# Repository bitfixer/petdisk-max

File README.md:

# petdisk-max
Firmware and schematics for the PETdisk MAX storage device for Commodore PET

The PETdisk MAX is a storage device for the Commodore PET series of computers. It can use both a microSD card and can also access up to 4 network drives.
The network drives are essentially directories of files hosted on standard web servers. They can be configured as read/write or readonly. Currently PHP support is required on a web server to be used as a network drive - simply copy the [petdisk.php](https://raw.githubusercontent.com/bitfixer/petdisk-max/main/www/petdisk.php) file into a directory on a web server along with some PET files, and you're ready to go.

## Installation

The PETdisk MAX plugs into the IEEE-488 port on the back of your PET. Looking at the back of the PET, this is the edge connector on the right side.
Since the IEEE-488 port does not supply power, a separate power connection is required.
Depending on when you received your PETdisk MAX, this will either be a small board which fits into one of the PET's ROM sockets and provides a 5v power pin, or a clip which connects to the PETdisk with a wire lead.

First, open up the PET.

### For the ROM socket: 
If you have any ROM sockets free, choose the one closest to the PETdisk and install the board into the socket on the mainboard, making sure to align the notches on both sockets. 
If no ROM sockets are free, first remove a ROM chip from the mainboard, install the socket, and then reinstall the ROM chip into the new socket. Make sure to line the notches up.
Then connect the wire lead included with the PETdisk to the 5v pin, and feed the other end out the back of the PET through the opening around the IEEE-488 connector.

### For the clip: 
You'll need to clip onto a 5v source on the mainboard. An easy place to find this is on one of the 6520 chips, there are 2 of them in the PET. They are located close on the board to the IEEE-488 port. Locate one of the 6520 chips, they will be close to the back of the board and labeled '6520' somewhere on the chip. Not to be confused with the '6502' also on the board.

Locations of 6520s in some PET motherboards:\
2001: UB8 and UG8\
2001N: UC6 and UC7\
8032: UB16 and UB12

Pick the more conveniently located 6520, and find pin 20. If you are looking at the chip with the notch up, go to the left side of the chip and go down to the lower left corner. Clip on to this pin and then feed the wire lead out the back through the opening around the IEEE-488 connector.
If you prefer, you can clip on to any capacitor lead connected to 5v in the computer, there are several. 

Moving to the back of the PET, connect the wire lead to the PETdisk MAX. There is a connector on the back of the PETdisk, and the position on the connector furthest to the right side of the device is labeled '5v'. Connect here, double check that you are connected in the furthest right position, closest to the edge of the board.

After this, just plug the PETdisk MAX into the IEEE-488 connector and you're ready to go.

## Configuration

The default configuration of the PETdisk MAX uses the built-in sd card as device 8.
You can change this device number as well as setting up a maximum of 4 network drives by editing this file template:
[PETDISK.CFG](https://raw.githubusercontent.com/bitfixer/petdisk-max/main/PETDISK.CFG)\
Each line of the file consists of the drive number, comma, text specifying the drive.
SD0 refers to the built-in SD card. Change the drive number here if you like.
For network drives, the specifier is the full URL of the drive script. Up to 4 can be used at once.
Remove any lines with URLs if you don't want to use any network drives at that time.

The last 2 lines of the file contain the ssid and password for your wifi network, replace the placeholders with the information for your network. Note that only 2.4 Ghz wifi networks are supported.

Copy the edited file onto the root directory of your SD card. On the next power up, the new configuration will be read.

## Operation

Basic drive operations are the same as other Commodore storage devices.
Load a directory with
LOAD"$",devicenumber
and 
LIST

For BASIC 4, the CATALOG and DIRECTORY commands will also work.

Load a program (.PRG) with
LOAD"PROGRAM",devicenumber

or save with
SAVE"PROGRAM",devicenumber

The DLOAD command also works.

## Subdirectories

To change directories on a FAT32 volume, use
LOAD"$:dirname",devicenumber

This also loads the directory listing of the new directory.

Return to the previous directory with
LOAD"$:..",devicenumber

## D64

The PETdisk MAX currently supports D64 files for both reading and writing.
To mount a D64 file stored on either an SD card or network drive,
use the following command:
LOAD"$:filename.d64",devicenumber

This will mount the D64 file as the disk for the specified device number. It will also load the directory of the disk image which can be viewed with LIST.

To unmount the D64 file and return to the original device, use
LOAD"$:..",devicenumber

## Updating the PETdisk MAX

Firmware updates will come periodically with fixes and new features. The latest firmware for both the v1 and v2 PETdisk MAX models will be located here:\
PETdisk MAX v1 (Atmel ATmega1284)
[FIRMWARE.BIN](https://github.com/bitfixer/petdisk-max/raw/main/firmware/FIRMWARE.BIN)

PETdisk MAX v2 (ESP32):
[FIRMWARE.PD2](https://github.com/bitfixer/petdisk-max/raw/main/firmware/FIRMWARE.PD2)

To update the firmware on the device, copy this file onto the root directory of an empty microSD card formatted to FAT32. Insert the card into the PETdisk and power up. On the v1, the new firmware will be loaded onto the device after a few seconds. On the v2, the update takes about a minute during which you will first see rapid blinking on the LED, then a single blink every few seconds, followed by a few additional blinks and then the LED remains on. Once the LED is solidly on, the update is done.\
You can verify that the update worked by loading a directory from the SD card. 
At the end of the directory listing the git commit id will be listed, so you can verify it changed from before the update. This also provides a firmware ID which you can use if you need to report any bugs.

## Building the PETdisk MAX firmware

If you want to build the PETdisk MAX firmware, two versions are included in this repo. The first is a legacy version built with platformio and arduino, and is located in the 'legacy' directory. Open that directory in VSCode with the platformio plugin installed, and you should be able to build and install with the platformio menu. 
Second is a newer version built directly on esp-idf v5.1+. This is located in the 'idf' directory. With esp-idf 5.1+ installed and sourced, run 'idf.py build flash' to build and install the firmware on the device.

## Coming Soon

Things known to currently not work (but working on it):
1. Support for BASIC 1 ROM (i.e. non-upgraded original PET 2001)
2. REL files
3. U2 (block write) drive command

Please let me know if you discover any bugs or have feature requests.
bitfixer at (removeforantispam) bitfixer dot com

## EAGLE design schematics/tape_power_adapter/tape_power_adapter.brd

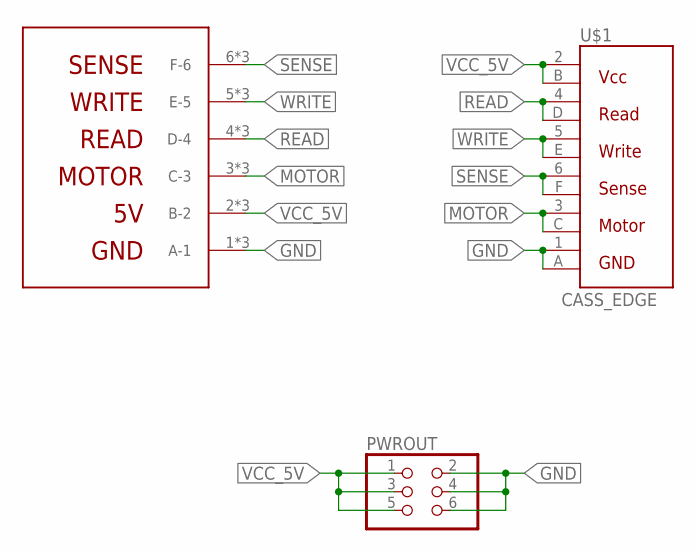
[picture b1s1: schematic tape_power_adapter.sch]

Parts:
PWROUT: PINHD-2X03_2.54; 2X03
U$1: CASS_EDGE; 12PINEDGE
U$2: C64CASSCONN; C64TAPECONN

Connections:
GND: PWROUT.2, PWROUT.4, PWROUT.6, U$1.1 (GND1), U$1.A (GND2), U$2.1 (A-1), U$2.1A (A-1), U$2.A (A-1)
MOTOR: U$1.3 (MOTOR1), U$1.C (MOTOR2), U$2.3 (C-3), U$2.3C (C-3), U$2.C (C-3)
READ: U$1.4 (READ1), U$1.D (READ2), U$2.4 (D-4), U$2.4D (D-4), U$2.D (D-4)
SENSE: U$1.6 (SENSE1), U$1.F (SENSE2), U$2.6 (F-6), U$2.6F (F-6), U$2.F (F-6)
VCC_5V: PWROUT.1, PWROUT.3, PWROUT.5, U$1.2 (VCC1), U$1.B (VCC2), U$2.2 (B-2), U$2.2B (B-2), U$2.B (B-2)
WRITE: U$1.5 (WRITE1), U$1.E (WRITE2), U$2.5 (E-5), U$2.5E (E-5), U$2.E (E-5)

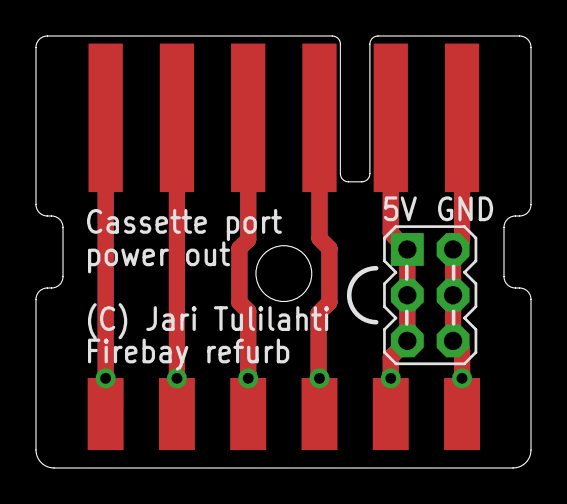
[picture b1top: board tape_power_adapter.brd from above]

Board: 2 copper layers, 27.5 x 24.0 mm, 3 parts (0 on the bottom side), 6 nets.

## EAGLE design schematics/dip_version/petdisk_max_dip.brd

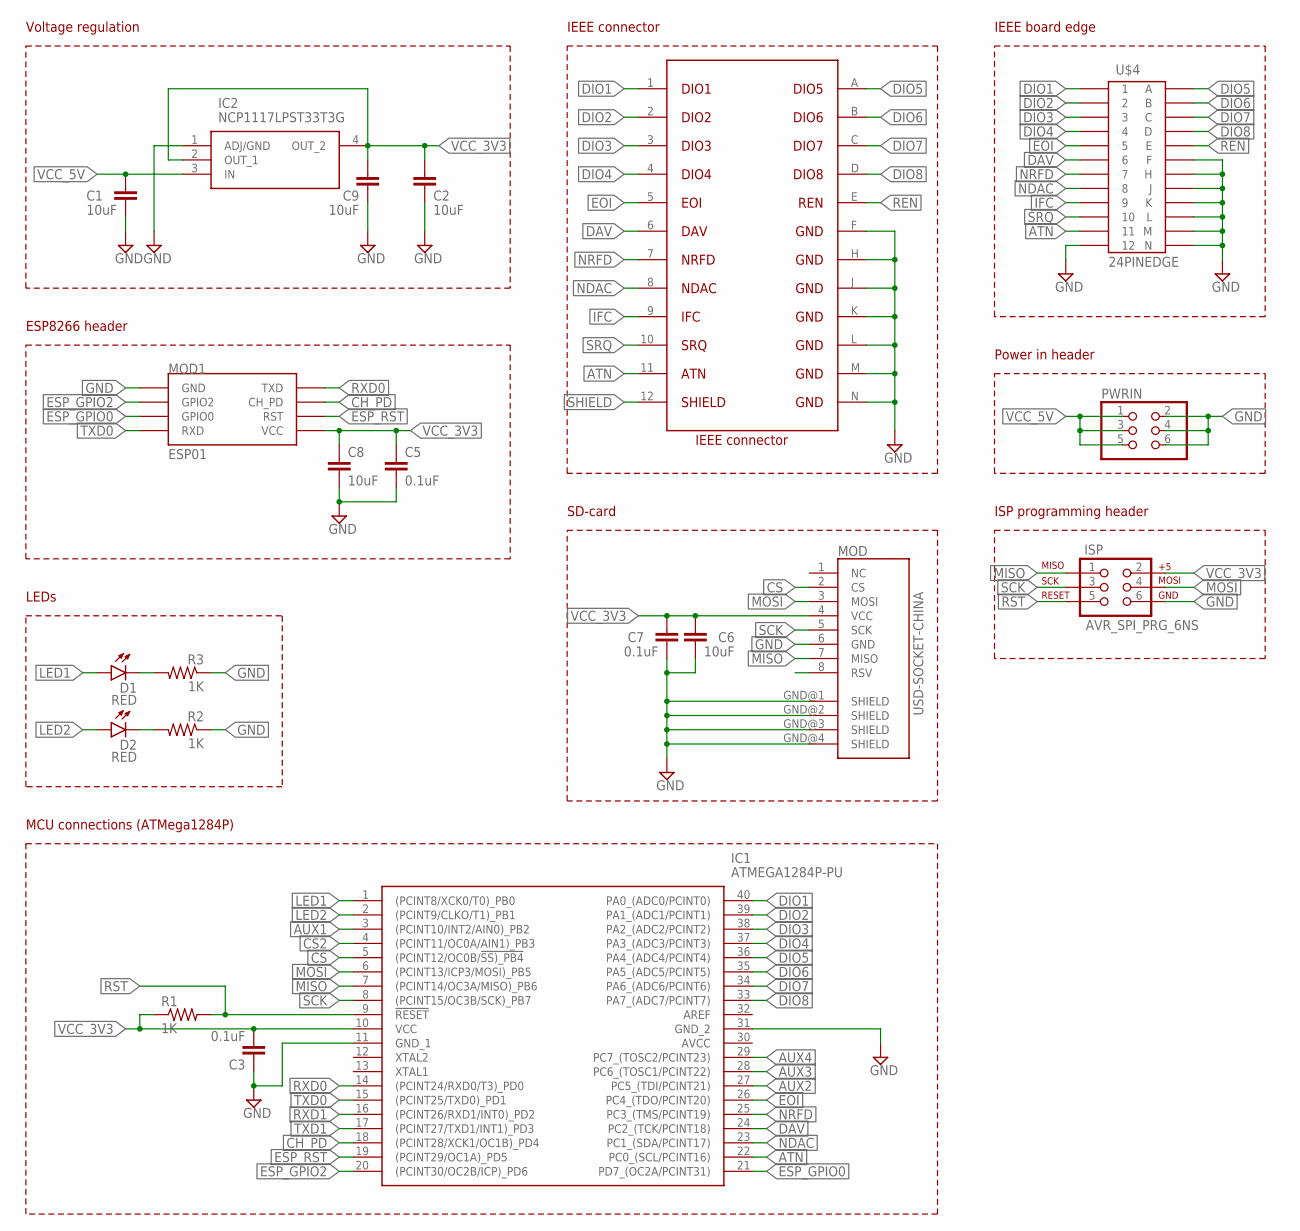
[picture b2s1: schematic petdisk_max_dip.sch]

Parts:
C1, C2, C6, C8, C9: 10uF; 1206
C3, C5, C7: 0.1uF; 0603-CAP
D1, D2: RED; LED-0603
IC1: ATMEGA1284P-PU; DIP1543W58P254L5175H635Q40N
IC2: NCP1117LPST33T3G; SOT230P700X180-4N
ISP: AVR_SPI_PRG_6NS; 2X3-NS
MOD: USD-SOCKET-CHINA; USD-SOCKET-PP
MOD1: ESP01
PWRIN: PINHD-2X03_2.54; 2X03
R1, R2, R3: 1K; 0603-RES
U$1: CBM_IEEE_CONN; UPS24CONN
U$4: 24PINEDGE

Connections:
ATN: IC1.22 (PC0_(SCL/PCINT16)), U$1.11, U$4.11
AUX1: IC1.3 ((PCINT10/INT2/AIN0)_PB2)
AUX2: IC1.27 (PC5_(TDI/PCINT21))
AUX3: IC1.28 (PC6_(TOSC1/PCINT22))
AUX4: IC1.29 (PC7_(TOSC2/PCINT23))
CH_PD: IC1.18 ((PCINT28/XCK1/OC1B)_PD4), MOD1.CH_PD
CS: IC1.5 ((PCINT12/OC0B/!SS)_PB4), MOD.2 (CS)
CS2: IC1.4 ((PCINT11/OC0A/AIN1)_PB3)
DAV: IC1.24 (PC2_(TCK/PCINT18)), U$1.6, U$4.6
DIO1: IC1.40 (PA0_(ADC0/PCINT0)), U$1.1, U$4.1
DIO2: IC1.39 (PA1_(ADC1/PCINT1)), U$1.2, U$4.2
DIO3: IC1.38 (PA2_(ADC2/PCINT2)), U$1.3, U$4.3
DIO4: IC1.37 (PA3_(ADC3/PCINT3)), U$1.4, U$4.4
DIO5: IC1.36 (PA4_(ADC4/PCINT4)), U$1.A, U$4.A
DIO6: IC1.35 (PA5_(ADC5/PCINT5)), U$1.B, U$4.B
DIO7: IC1.34 (PA6_(ADC6/PCINT6)), U$1.C, U$4.C
DIO8: IC1.33 (PA7_(ADC7/PCINT7)), U$1.D, U$4.D
EOI: IC1.26 (PC4_(TDO/PCINT20)), U$1.5, U$4.5
ESP_GPIO0: IC1.21 (PD7_(OC2A/PCINT31)), MOD1.GPIO0
ESP_GPIO2: IC1.20 ((PCINT30/OC2B/ICP)_PD6), MOD1.GPIO2
ESP_RST: IC1.19 ((PCINT29/OC1A)_PD5), MOD1.RST
GND: C1.2, C2.2, C3.1, C5.2, C6.2, C7.2, C8.2, C9.2, IC1.11 (GND_1), IC1.31 (GND_2), IC2.1 (ADJ/GND), ISP.6, MOD.6 (GND), MOD.GND@1 (SHIELD), MOD.GND@2 (SHIELD), MOD.GND@3 (SHIELD), MOD.GND@4 (SHIELD), MOD1.GND, PWRIN.2, PWRIN.4, PWRIN.6, R2.1, R3.1, U$1.F, U$1.H, U$1.J, U$1.K, U$1.L, U$1.M, U$1.N, U$4.12, U$4.F, U$4.H, U$4.J, U$4.K, U$4.L, U$4.M, U$4.N
IFC: U$1.9, U$4.9
LED1: D1.A, IC1.1 ((PCINT8/XCK0/T0)_PB0)
LED2: D2.A, IC1.2 ((PCINT9/CLKO/T1)_PB1)
MISO: IC1.7 ((PCINT14/OC3A/MISO)_PB6), ISP.1, MOD.7 (MISO)
MOSI: IC1.6 ((PCINT13/ICP3/MOSI)_PB5), ISP.4, MOD.3 (MOSI)
unnamed: D1.C, R3.2
unnamed: D2.C, R2.2
NDAC: IC1.23 (PC1_(SDA/PCINT17)), U$1.8, U$4.8
NRFD: IC1.25 (PC3_(TMS/PCINT19)), U$1.7, U$4.7
REN: U$1.E, U$4.E
RST: IC1.9 (!RESET), ISP.5, R1.2
RXD0: IC1.14 ((PCINT24/RXD0/T3)_PD0), MOD1.TX (TXD)
RXD1: IC1.16 ((PCINT26/RXD1/INT0)_PD2)
SCK: IC1.8 ((PCINT15/OC3B/SCK)_PB7), ISP.3, MOD.5 (SCK)
SHIELD: U$1.12
SRQ: U$1.10, U$4.10
TXD0: IC1.15 ((PCINT25/TXD0)_PD1), MOD1.RX (RXD)
TXD1: IC1.17 ((PCINT27/TXD1/INT1)_PD3)
VCC_3V3: C2.1, C3.2, C5.1, C6.1, C7.1, C8.1, C9.1, IC1.10 (VCC), IC2.2 (OUT_1), IC2.4 (OUT_2), ISP.2, MOD.4 (VCC), MOD1.VCC, R1.1
VCC_5V: C1.1, IC2.3 (IN), PWRIN.1, PWRIN.3, PWRIN.5

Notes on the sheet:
Voltage regulation
IEEE connector
ESP8266 header
MCU connections (ATMega1284P)
SD-card
LEDs
IEEE board edge
Power in header
ISP programming header

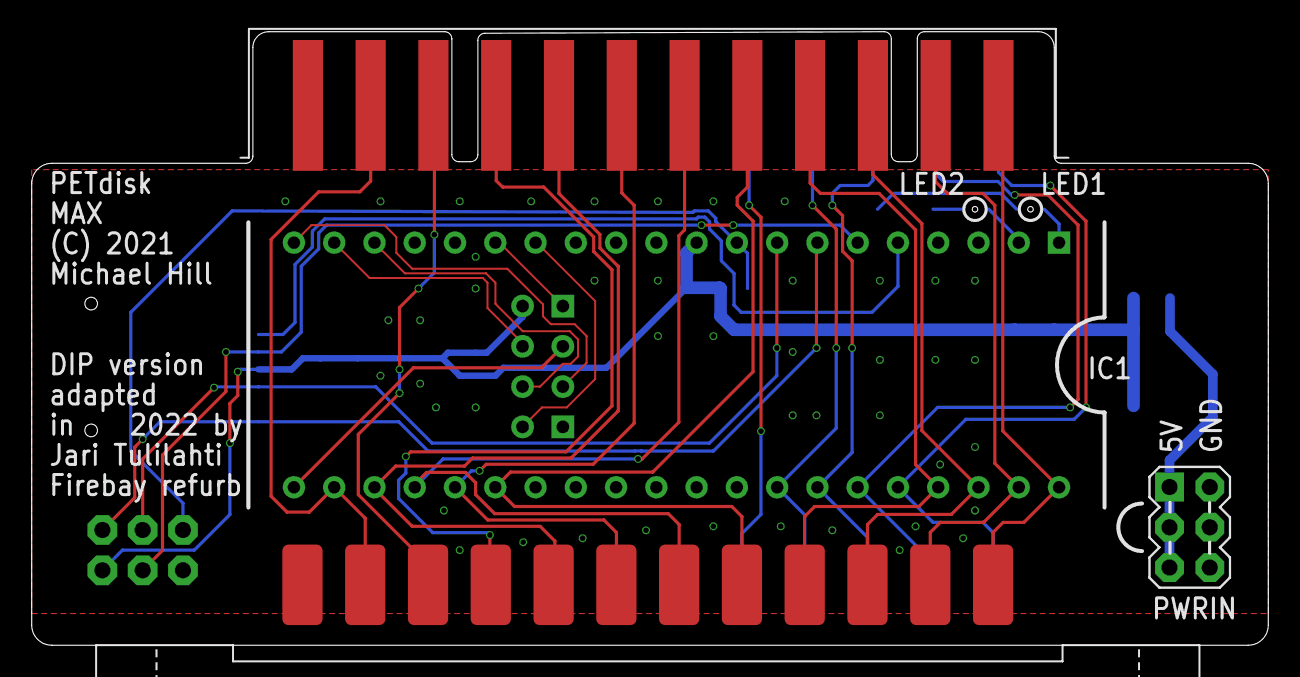
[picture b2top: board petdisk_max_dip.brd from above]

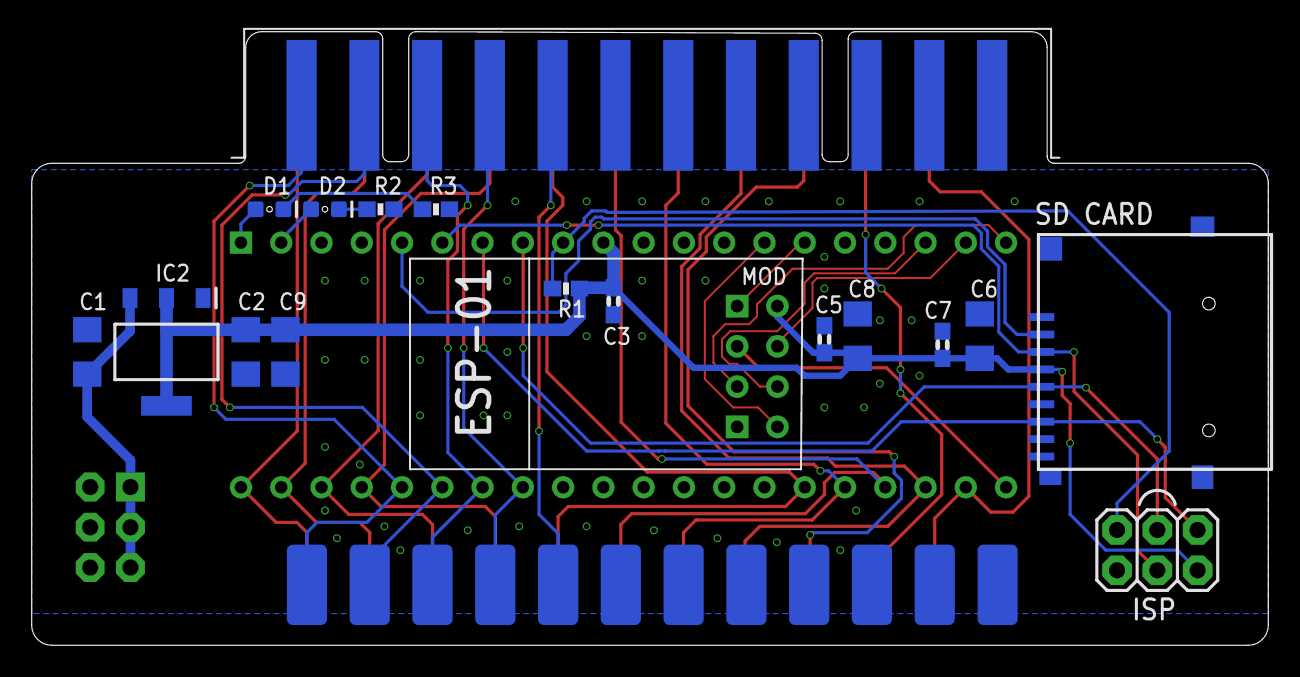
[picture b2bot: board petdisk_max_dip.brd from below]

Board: 2 copper layers, 78.0 x 38.7 mm, 21 parts (17 on the bottom side), 34 nets.

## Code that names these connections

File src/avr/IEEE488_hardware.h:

#ifndef __IEEE488_HARDWARE_H__
#define __IEEE488_HARDWARE_H__

#include <avr/io.h>

#define IEEE_PORT   PORTC
#define IEEE_PIN    PINC
#define IEEE_CTL    DDRC

#define DATA_PORT   PORTA
#define DATA_PIN    PINA
#define DATA_CTL    DDRA

#define ATN_PIN     PC0
#define NDAC_PIN    PC1
#define DAV_PIN     PC2
#define NRFD_PIN    PC3
#define EOI_PIN     PC4

#define ATN_MASK        1<<ATN_PIN
#define NOT_ATN_MASK    ~(ATN_MASK)

#define DAV_MASK        1<<DAV_PIN
#define NOT_DAV_MASK    ~(DAV_MASK)

#define EOI_MASK        1<<EOI_PIN
#define NOT_EOI_MASK    ~(EOI_MASK)

#define NRFD_MASK       1<<NRFD_PIN
#define NOT_NRFD_MASK   ~(NRFD_MASK)

#define NDAC_MASK       1<<NDAC_PIN
#define NOT_NDAC_MASK   ~(NDAC_MASK)

#define lower_eoi()     IEEE_PORT &= NOT_EOI_MASK
#define lower_dav()     IEEE_PORT &= NOT_DAV_MASK
#define lower_nrfd()    IEEE_PORT &= NOT_NRFD_MASK
#define lower_ndac()    IEEE_PORT &= NOT_NDAC_MASK

#define raise_eoi()     IEEE_PORT |= EOI_MASK
#define raise_dav()     IEEE_PORT |= DAV_MASK
#define raise_nrfd()    IEEE_PORT |= NRFD_MASK
#define raise_ndac()    IEEE_PORT |= NDAC_MASK

#define read_atn()      (IEEE_PIN & ATN_MASK)
#define read_eoi()      (IEEE_PIN & EOI_MASK)
#define read_dav()      (IEEE_PIN & DAV_MASK)
#define read_nrfd()     (IEEE_PIN & NRFD_MASK)
#define read_ndac()     (IEEE_PIN & NDAC_MASK)

#define set_atn_input()     IEEE_CTL &= NOT_ATN_MASK
#define set_eoi_input()     IEEE_CTL &= NOT_EOI_MASK
#define set_dav_input()     IEEE_CTL &= NOT_DAV_MASK
#define set_nrfd_input()    IEEE_CTL &= NOT_NRFD_MASK
#define set_ndac_input()    IEEE_CTL &= NOT_NDAC_MASK

#define set_eoi_output()     IEEE_CTL |= EOI_MASK
#define set_dav_output()     IEEE_CTL |= DAV_MASK
#define set_nrfd_output()    IEEE_CTL |= NRFD_MASK
#define set_ndac_output()    IEEE_CTL |= NDAC_MASK
#define set_datadir_output()

#define ieee_read_data_byte(recvByte)   recvByte = DATA_PIN
#define ieee_write_data_byte(byte)      DATA_PORT = byte
#define ieee_set_data_output()          DATA_CTL = 0xFF
#define ieee_set_data_input()           DATA_CTL = 0x00


#endif

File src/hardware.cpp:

#include "hardware.h"

#include <stdio.h>
#include <util/delay.h>
#include <avr/io.h>
#include <avr/interrupt.h>
#include <avr/pgmspace.h>
#include <avr/eeprom.h>

#define ESP_CONTROL     DDRD
#define ESP_PORT        PORTD
#define ESP_CH_PD       PD4
#define ESP_RST         PD5
#define ESP_GPIO0       PD7
#define ESP_GPIO2       PD6

#define LED_CONTROL     DDRB
#define LED_PORT        PORTB
#define LED_PIN1        PB0
#define LED_PIN2        PB1

#define SPI_CONTROL     DDRB
#define SPI_PORT        PORTB
#define SPI_CS          PB4
#define SPI_CS2         PB3
#define SPI_MOSI        PB5
#define SPI_SCK         PB7

#define SPI_CS_MASK     1<<SPI_CS
#define NOT_SPI_CS_MASK ~(SPI_CS_MASK)

uint8_t spi_cs()
{
    return SPI_CS;
}

void prog_init()
{
     // set reset for esp
    ESP_PORT = (1 << ESP_CH_PD) | (1 << ESP_RST);
    ESP_CONTROL = (1 << ESP_CH_PD) | (1 << ESP_RST);
    sei();
}

void reset_esp()
{
    ESP_PORT &= ~(1 << ESP_RST);
    ESP_PORT &= ~(1 << ESP_CH_PD);

    for (int i = 0; i < 20; i++)
    {
        _delay_loop_2(65535);
    }

    ESP_PORT |= 1 << ESP_RST;
    ESP_PORT |= 1 << ESP_CH_PD;
}

void init_led()
{
    LED_CONTROL |= 1 << LED_PIN1;
    LED_CONTROL |= 1 << LED_PIN2;
}

void set_led(bool value)
{
    if (value == true)
    {
        LED_PORT |= 1 << LED_PIN1;
        LED_PORT |= 1 << LED_PIN2;
    }
    else
    {
        LED_PORT &= ~(1 << LED_PIN1);
        LED_PORT &= ~(1 << LED_PIN2);
    }
}

void hDelayMs(int ms)
{
    for (int i = 0; i < ms; i++)
    {
        _delay_ms(1);
    }
}

uint8_t bf_pgm_read_byte(uint8_t* src)
{
  return pgm_read_byte(src);
}

void bf_eeprom_write_block(const void* block, void* eeprom, size_t n)
{
    eeprom_write_block(block, eeprom, n);
}

void bf_eeprom_read_block(void* block, const void* eeprom, size_t n)
{
    eeprom_read_block(block, eeprom, n);
}

uint8_t bf_eeprom_read_byte(const uint8_t* addr)
{
    return eeprom_read_byte(addr);
}

// SPI

void spi_init()
{
    SPI_PORT = 0x00;
    SPI_PORT |= 1 << SPI_CS;
    SPI_PORT |= 1 << SPI_CS2;
    SPI_CONTROL |= 1 << SPI_CS;
    SPI_CONTROL |= 1 << SPI_CS2;
    SPI_CONTROL |= 1 << SPI_MOSI;
    SPI_CONTROL |= 1 << SPI_SCK; 

    SPCR = 0x52;
    SPSR = 0x00;
}

uint8_t spi_transmit(uint8_t data)
{
    SPDR = data;
    while ( !(SPSR & (1<<SPIF)) ) {}

    data = SPDR;
    return data;
}

void spi_cs_select()
{
    SPI_PORT &= NOT_SPI_CS_MASK;
}

void spi_cs_unselect()
{
    SPI_PORT |= SPI_CS_MASK;
}

// serial

uint32_t bRnd(float f)
{
    uint32_t i = (uint32_t)f;
    float r = f - (float)i;

    if (r >= 0.5f)
    {
        return i+1;
    }
    else
    {
        return i;
    }
}

uint8_t ubrrFromBaudRate(uint32_t baudRate, bool* doubleSpeed)
{
    // try regular speed first
    float fRegUbrr = (float(F_CPU) / float(16*baudRate)) - 1.0f;
    uint32_t regUbrr = bRnd(fRegUbrr);
    // get real baud rate
    uint32_t actualRegBr = (float(F_CPU) / float(16*(regUbrr+1)));
    float regErr = 1.0 - (float)actualRegBr / (float)baudRate;
    if (regErr < 0.0) {
        regErr = -regErr;
    }

    // try double speed
    float fDblUbrr = (float(F_CPU) / float(8*baudRate)) - 1.0f;
    uint32_t dblUbrr = bRnd(fDblUbrr);
    // get real baud rate
    uint32_t actualDblBr = (F_CPU / (8*(dblUbrr+1)));
    float dblErr = 1.0 - (float)actualDblBr / (float)baudRate;
    if (dblErr < 0.0) {
        dblErr = -dblErr;
    }

    if (regErr <= dblErr) {
        *doubleSpeed = false;
        return (uint8_t)regUbrr;
    } else {
        *doubleSpeed = true;
        return (uint8_t)dblUbrr;
    }
}

void serial0_init(uint32_t baudRate)
{
    bool double_speed;
    uint8_t ubrr = ubrrFromBaudRate(baudRate, &double_speed);

    UBRR0H = (unsigned char)(ubrr>>8);
    UBRR0L = (unsigned char)ubrr;
    UCSR0A = double_speed ? (1<<U2X0) : 0x00;
    UCSR0B = (1<<RXEN0)|(1<<TXEN0);
    UCSR0C = (1<<USBS0)|(3<<UCSZ00);
}

void serial0_transmitByte(unsigned char data)
{
    while ( !(UCSR0A & (1<<UDRE0)) ) {}
    UDR0 = data;
}

unsigned char serial0_receiveByte()
{
    unsigned char data;
    while ( !(UCSR0A & (1<<RXC0)) ) {}
    data = UDR0;
    return(data);
}

void serial0_enable_interrupt()
{
    UCSR0B |= (1 << RXCIE0);
}

void serial0_disable_interrupt()
{
    UCSR0B &= ~(1 << RXCIE0);
}

void serial1_init(uint32_t baudRate)
{
    bool double_speed;
    uint8_t ubrr = ubrrFromBaudRate(baudRate, &double_speed);

    UBRR1H = (unsigned char)(ubrr>>8);
    UBRR1L = (unsigned char)ubrr;
    UCSR1A = double_speed ? (1<<U2X1) : 0x00;
    UCSR1B = (1<<RXEN1)|(1<<TXEN1);
    UCSR1C = (1<<USBS1)|(3<<UCSZ10);
}

void serial1_transmitByte(unsigned char data)
{
    while ( !(UCSR1A & (1<<UDRE1)) ) {}
    UDR1 = data;
}

unsigned char serial1_receiveByte()
{
    unsigned char data;
    while ( !(UCSR1A & (1<<RXC1)) ) {}
    data = UDR1;
    return(data);
}

void serial1_enable_interrupt()
{
    UCSR1B |= (1 << RXCIE1);
}

void serial1_disable_interrupt()
{
    UCSR1B &= ~(1 << RXCIE1);
}

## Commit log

2021-01-13 added source
2021-01-13 added Makefile and web server
2021-01-13 added bin directory
2021-01-13 some fixes to makefile
2021-01-13 cleaned up warnings
2021-01-22 Revert "cleaned up warnings"
    This reverts commit c6266e0a75b76358b566070883c531f17c334b18.
2021-01-23 change to atmega1284p in makefile
2021-02-06 added reset to makefile, fixed some warnings
2021-02-08 support DLOAD command, remove drive id from filename
2021-02-08 moved atn loop
2021-02-08 moved filename processing
2021-02-08 merged
2021-02-10 refactored petdisk run function
2021-02-10 WIP refactoring updated run method. Directory working but not load
2021-02-10 fixed bug in file loading
2021-02-10 WIP removed old run function, fixed processFilename. Does not return to idle after saving seq
2021-02-10 WIP adding support for reading SEQ
2021-02-11 WIP work on reading seq files
2021-02-11 cleanup
2021-02-12 fixed bug, should have lowered DAV in sendIEEEbyteCheckForATN
2021-02-12 cleanup and fixed behavior when no card is in the slot
2021-02-12 removing unused instance vars
2021-02-12 more ivar cleanup
2021-02-13 seq loading partially working
2021-02-13 fixed typo
2021-02-14 WIP adding multiple open file info structs, to track multiple open files
2021-02-16 WIP retaining next byte during seq read
2021-02-16 WIP fixed bug in recording secondary address
2021-02-16 SEQ reads from multiple files working
2021-02-16 cleanup, removed unnecessary variables
2021-02-17 fixed issue with writing seq files
2021-02-19 added D64 datasource
2021-02-20 WIP adding d64 stuff
2021-02-20 remove separate mem buffer in d64datasource
2021-02-20 WIP getting SEQ read working on D64
2021-02-20 WIP fixed read buffer size for d64
2021-02-20 fixed bug when storing address of data buffer
2021-02-20 fixed line endings
2021-02-21 directory semi-working on d64
2021-02-22 added ability to mount d64 drive from another datasource
2021-02-22 mount and unmount d64 file
2021-02-23 fixed bug in network sendData method
2021-02-23 seek working on network datasource, changed to 32 bit int
2021-02-25 set request sizes to 256 for d64 datasource using network
2021-02-25 fixed warnings
2021-02-28 WIP adding write function to d64
2021-03-01 WIP testing d64 writing
2021-03-02 WIP writing file to d64
2021-03-02 WIP file save mostly working on d64
2021-03-02 detect file type on write d64
2021-03-03 WIP file write works with directory entry
2021-03-03 getting logger working
2021-03-03 WIP more cleanup
2021-03-03 build errors
2021-03-04 added requestWriteBufferSize
2021-03-05 WIP support update in network ds
2021-03-05 wip debugging writing to d64 on network
2021-03-05 writing works d64 network
2021-03-05 cleanup, fixed unneeded fetch
2021-03-06 WIP block read works!
2021-03-07 fixed saving on network drive
2021-03-07 added more open file info structs
2021-03-08 fixed bugs with network file names, loading d64s not found
2021-03-20 added PETDISK.CFG
2021-03-20 added firmware image
2021-03-20 more readme updates
2021-03-20 more updates:
2021-03-23 turn on led after loading
2021-04-06 WIP implementing catalog command
2021-04-06 WIP sending directory bytes
2021-04-06 WIP something shows up with catalog
2021-04-07 WIP still working on reliable reading
2021-04-07 set eoi on last byte
2021-04-07 WIP loading through one entry ok
2021-04-07 slowing down the transfer helps?
2021-04-07 do not unlisten when ending output, seems to fix the catalog issue for now
2021-04-07 listing mostly working now
2021-04-07 last line of dir prints
2021-04-08 fixed line numbers
2021-04-08 can load regular dir as well
2021-04-08 formatting change for catalog
2021-04-08 change header for catalog
2021-04-09 added remainder byte, fixed extra byte problem
2021-04-09 removed unused fn
2021-04-09 catalog from d64 working on network
2021-04-09 more cleanup
2021-04-10 cleanup, merge catalog and load $ paths
2021-04-12 used larger string for connecting to wifi
2021-04-12 new firmware
2021-04-13 parse port from url string
2021-05-30 added schematics
2021-05-30 updated schematic
2021-08-24 fix for showing directories
2021-08-25 fixed virtual methods in datasource which were not being called
2021-08-25 updated firmware
2021-09-03 moved esp init outside of check for wifi creds
2021-09-03 move esp check before default
2021-09-03 fix bug. move init code
2021-09-03 log when esp present
2021-09-10 fix for directory bug, init was clobbering current directory cluster
2021-09-10 update firmware, directory loading fix
2021-09-11 fixed bug in string copy
2021-09-13 go to root cluster if directory cluster reads as 0
2021-09-13 firmware update
2021-09-13 moved setting unused sectors after directory check
2021-09-15 added port parsing to url string for networkdrive
2022-01-11 first working version after esp32 refactor
2022-01-12 baud rate setting and got esp-01 working
2022-01-12 some cleanup
2022-01-12 cleanup eeprom access
2022-01-12 moved serial hw specific stuff into hardware.cpp
2022-01-12 WIP integrating esp32 build, moving code
2022-01-14 respond to ATN during directory by lowering ndac faster, fixed problem with dir load
2022-01-18 cleanup and changed ATN and CS pins
2022-01-21 use pgmspace for esp32, cleanup
2022-01-21 moved main func for avr
2022-01-22 use pgm_read_byte
2022-01-25 attempt at sd ota update
2022-01-25 simplified and cleaned up sd updater
2022-01-25 sd update works
2022-01-26 PCB for ATMega1284p DIP-version, made with Eagle. Includes Gerbers.
2022-01-26 PCB for tape port power passthrough, made with Eagle. Includes Gerbers.
2022-01-26 Tape power adapter PCB, made with Eagle. Includes gerbers
2022-01-26 Add partlist
2022-01-27 added sd loader as separate target
2022-01-27 remove watchdog
2022-01-28 do not delete firmware file if NODELETE.FRM present
2022-01-28 move sd card update functions out of main program
2022-02-02 use old code for bootloader, unchanged
2022-02-02 changed location of bootloader
2022-02-02 fixed stat syntax in makefile
2022-02-03 default partitions
2022-02-03 added some led blinks to bootloader
2022-02-12 removed some comments
2022-02-12 get git hash again
2022-02-12 updated sd loader
2022-02-14 added setting FAT32 time from network data source
2022-02-14 added reset script for platformio
2022-02-14 remove duplicate request for time
2022-02-15 PCB for ATMega1284p DIP-version, made with Eagle. Includes Gerbers. (#6)
    * PCB for ATMega1284p DIP-version, made with Eagle. Includes Gerbers.
    * Add partlist
2022-02-15 Tape power adapter PCB, made with Eagle. Includes gerbers (#8)
2022-02-16 fix stat command
2022-02-17 made filesize tool for building cross-platform, fixed avr issue with extern buffer
2022-02-17 add delay after resetting esp
2022-02-17 fixed hardcoded number
2022-02-18 needed to return value from startClient
2022-02-28 treat files without extension as PRG
2022-03-04 added disable mode
2022-03-22 support wedge directory commands
2022-03-22 cd commands for d64
2022-03-23 wedge commands for cd working now
2022-03-25 change firmware file name for esp32 version
2022-04-22 move unused sector setting until after directory check
2022-05-17 update project file, use @ prefix to load d64
2022-07-07 added a script for starting containerized server serving files for PET from the www-directory
2022-08-15 fix avr build
2022-10-31 added petdisk max v2 schematic
2022-10-31 added notes
2022-12-27 specify espressif32 platform version
2023-06-18 change to idf 4.0
2023-07-29 script fixes
2023-07-29 Revert "change to idf 4.0"
    This reverts commit cf2dc839bf0163e1c87da99d52c71a69657f0326.
2023-07-29 fixed init of network data source
2023-07-29 Revert "Revert "change to idf 4.0""
    This reverts commit 5ad24cb6f6790460e887901ed5f9e594f6736730.
2023-07-30 guard against buffer overflow in espConn
2023-08-09 different frameworks for sd_loader and petdisk
2023-08-10 Revert "different frameworks for sd_loader and petdisk"
    This reverts commit 275c9e9d205cee63d39655ab769179abf2e22230.
2023-08-31 add base64 decoding for save files
2024-03-31 move legacy code
2024-03-31 import idf version
2024-04-17 added HTTPClient
2024-04-17 fixed csv parsing, remove \r character
2025-01-10 make sure to use default configuration if no devices are set
2025-01-10 extract settings to sdkconfig.defaults
2025-03-27 added console
2025-03-28 console commands
2025-03-28 more test functions
2025-03-28 led test functions
2025-03-29 fix gpio for s2
2025-03-29 WIP new http datasource
2025-03-30 new http stuff
2025-03-31 http datasource testing
2025-03-31 testing for http ds and psram
2025-04-04 fix s2 pins
2025-04-04 usb cdc console, testing without psram
2025-04-06 reading works, faster io
2025-04-06 pin defs
2025-04-07 optimize esp32s2 gpio
2025-04-08 test and datadir
2025-04-16 disable interrupts, first load fix
2025-04-25 atn in isr
2025-04-25 Adding support for esp32-s2 with petdisk (#15)
    * added console
    * console commands
    * more test functions
    * led test functions
    * fix gpio for s2
    * WIP new http datasource
2025-04-25 platform defaults
2025-04-25 move option
2025-04-25 more config
2025-04-25 esp32 changes
2025-04-25 flash size
2025-04-25 simplify atn wait
2025-04-25 1000 hz rtos
2025-04-26 Revert "simplify atn wait"
    This reverts commit 71fb65469f8b745354c8b24662cafc46ba5d572d.
2025-04-26 atn isr improvement
2025-04-26 removed some fn
2025-04-29 fix for dir state after opening
2025-04-30 simplify
2025-04-30 malloc for esp32 crash fix
2025-05-09 disable interrupts for esp32, loading better
2025-05-13 Revert "disable interrupts for esp32, loading better"
    This reverts commit 715cf07410be6d4e3c7f957cb8d5a760885bc049.
2025-05-13 no disabling interrupts
2025-05-13 network loading on esp32 working better
2025-05-13 logging after fetch seems to work?
2025-05-14 use xTaskNotifyGive
2025-05-14 network improvements
2025-05-14 unused var
2025-05-14 set led, fix interrupt crash
2025-05-21 added esp-fast-gpio
2025-05-21 moving gpio to lib
2025-05-21 input/output mask
2025-05-21 added esp-fast-gpio library, rework io (#16)
    * added esp-fast-gpio
    * moving gpio to lib
    * cleanup
    * more cleanup
    * input/output mask
2025-05-27 use high register operations
2025-05-27 some more cleanup
2025-05-28 clean up esp32 data macros
2025-05-28 add timeout to atn high, prevents getting stuck if pet is off
2025-05-30 pinspeed command
2025-05-31 updated macros
2025-05-31 bump
2025-05-31 clean up spi
2025-05-31 use spi interface
2025-09-05 ignore some files
2025-09-05 faster ndac lower
2025-09-05 fast set of ndac
2025-09-27 timeout reading dav low
2025-09-27 timeouts for dav
2025-09-28 remove unused
2025-09-28 timeout on atn high
2025-09-28 build fix
2025-09-28 more timeout
2025-09-28 more timeout handling
2025-10-01 fix esp32 build
2025-11-24 improved build, include sd loader in makefile
2025-11-24 automate build assembly
2025-11-24 add flash target
2025-11-25 fix main.bin
2025-11-25 change dir listing header per chip
2026-05-29 moved petdisk config, removed unused cmake file
2026-05-29 wip sdfat partially working
2026-05-29 use long filenames for fatfs
2026-05-29 added card detect interrupt
2026-05-29 attempt at rebuilding FAT32 datasource with IDF fatfs
2026-05-29 added card detect pin for esp32
2026-05-29 added a script for starting containerized server serving files for PET from the www-directory (#9)
2026-05-29 Refactor sdfat (#21)
    * attempt at rebuilding FAT32 datasource with IDF fatfs
    * wip sdfat partially working
    * use long filenames for fatfs
    * added card detect interrupt
    * added card detect pin for esp32
    ---------

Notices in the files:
parts and their libraries:
SparkFun-LED: Licensing: Creative Commons ShareAlike 4.0 International - https://creativecommons.org/licenses/by-sa/4.0
